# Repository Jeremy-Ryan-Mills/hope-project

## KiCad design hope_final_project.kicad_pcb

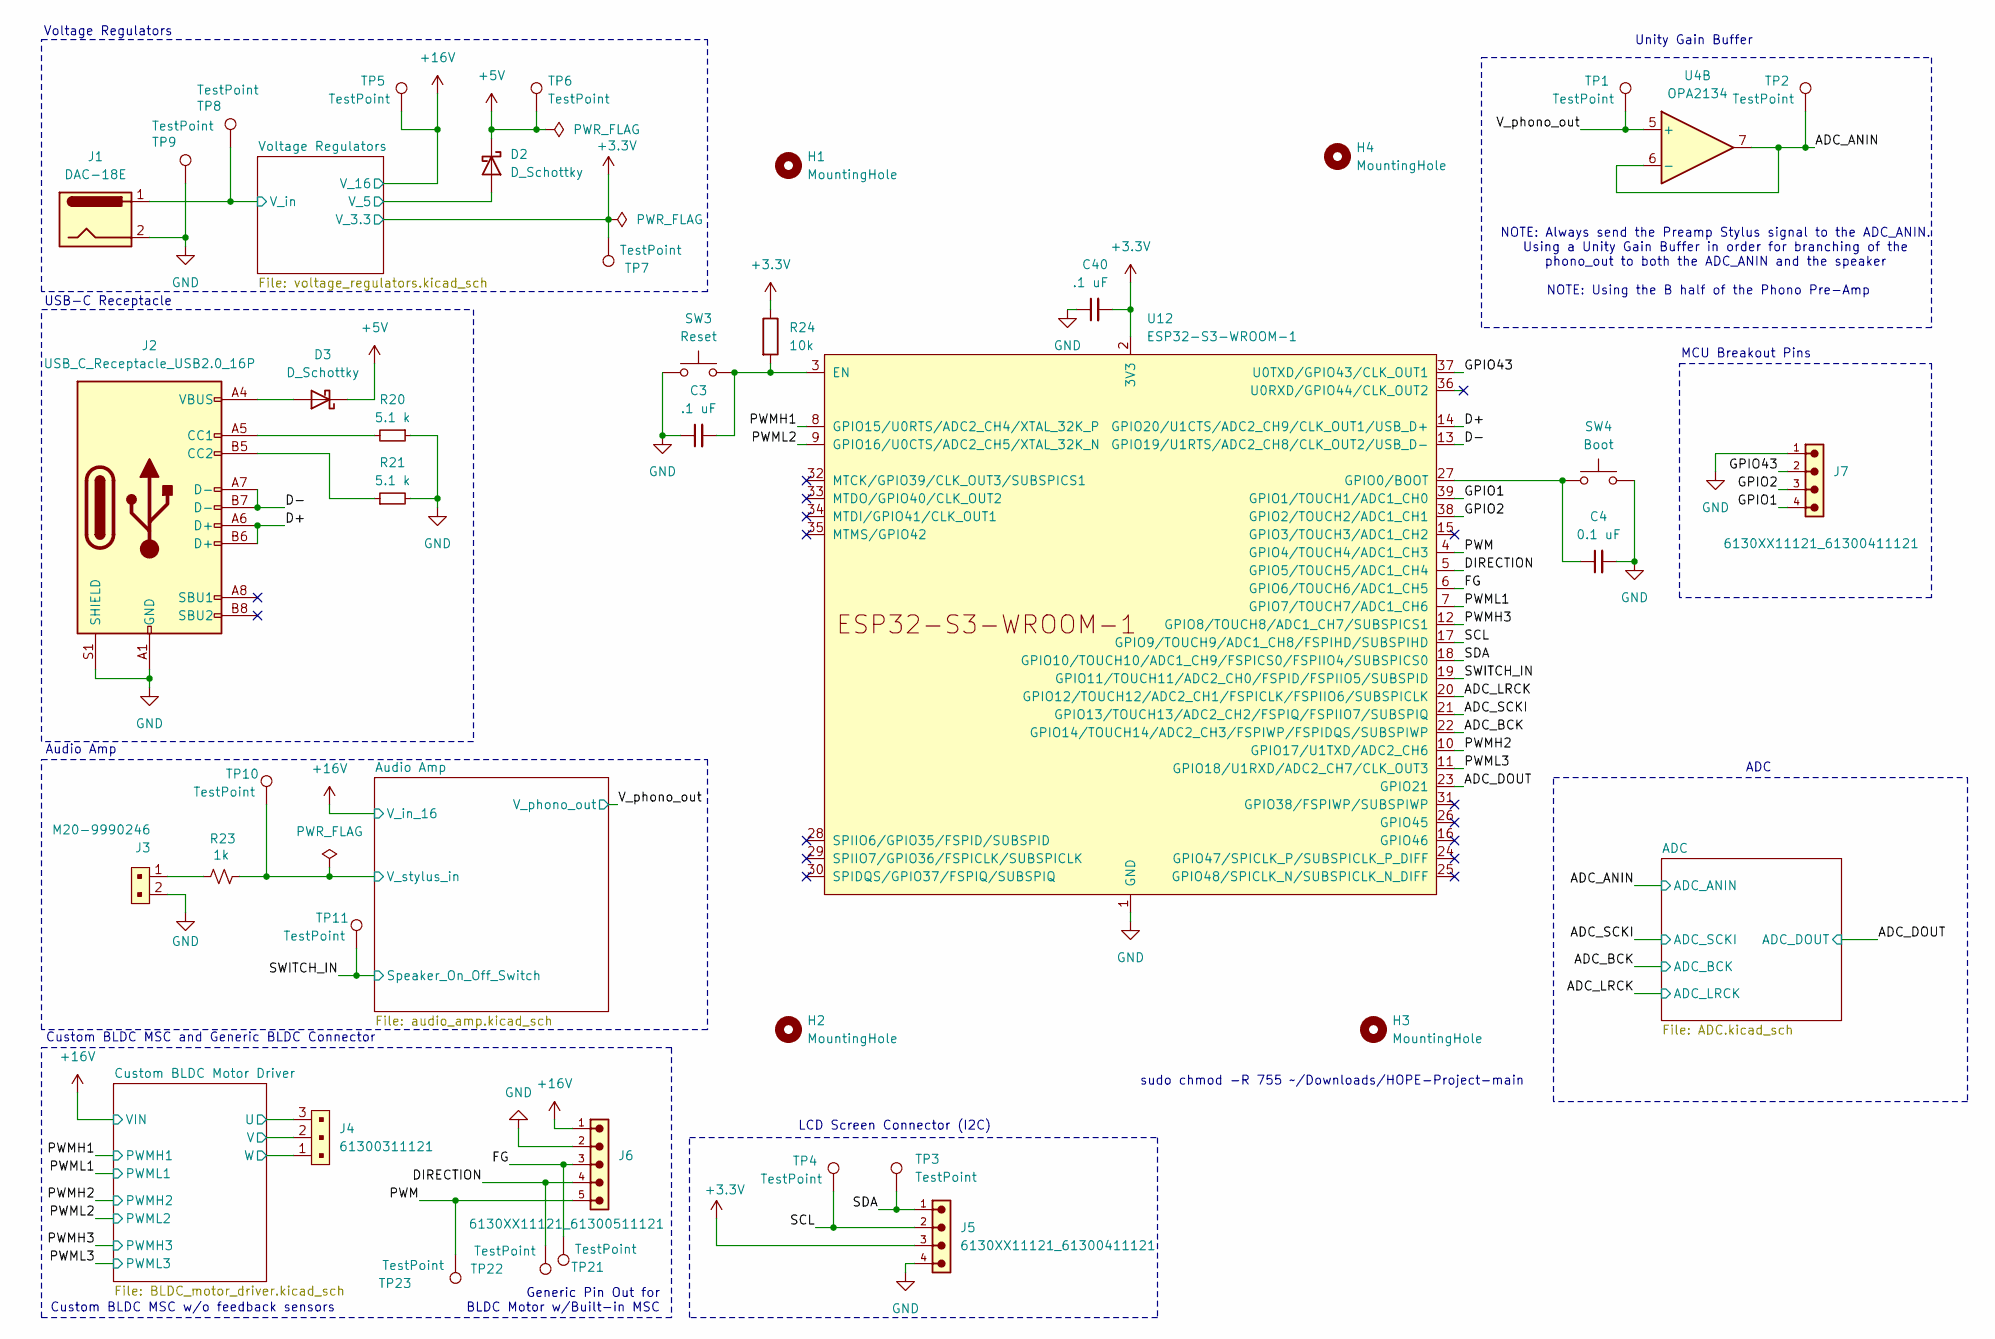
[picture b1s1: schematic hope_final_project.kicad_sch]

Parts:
C3, C40: .1 uF; C_0805_2012Metric
C4: 0.1 uF; C_0805_2012Metric
D2, D3: D_Schottky; D_SOD-123F
H1, H2, H3, H4: MountingHole; MountingHole_3.2mm_M3
J1: DAC-18E; PJ_002B
J2: USB_C_Receptacle_USB2.0_16P; GCT_USB4105GFA120
J3: M20-9990246; PinHeader_1x2_P2.54mm; MPN M20-9990246; Digi-Key_PN 952-2262-ND
J4: 61300311121; PinHeader_1x3_P2.54_Drill1.1mm; MPN 61300311121; Digi-Key_PN 732-5316-ND
J5, J7: 6130XX11121_61300411121; 61300411121; PART-NUMBER 61300411121
J6: 6130XX11121_61300511121; 61300511121; PART-NUMBER 61300511121
R20, R21: 5.1 k; R_0805_2012Metric
R23: 1k; R_0805_2012Metric
R24: 10k; R_0805_2012Metric
SW3: Reset; TL3301_A_G_EWI
SW4: Boot; TL3301_A_G_EWI
TP1, TP2, TP3, TP4, TP5, TP6, TP7, TP8, TP9, TP10, TP11, TP21, TP22, TP23: TestPoint; TestPoint_Pad_1.5x1.5mm
U4: OPA2134; SOIC-8_W3.9mm
U12: ESP32-S3-WROOM-1

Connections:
+3.3V: C40.2, J5.3, R24.1, TP7.1, U12.2 (3V3); also elsewhere on the board
+5V: D2.1 (K), D3.1 (K), TP6.1; also elsewhere on the board
+16V: J6.1, TP5.1; also elsewhere on the board
/ADC_ANIN: TP2.1, U4.6 (-), U4.7; also elsewhere on the board
/ADC_BCK: U12.22 (GPIO14/TOUCH14/ADC2_CH3/FSPIWP/FSPIDQS/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); also elsewhere on the board
/ADC_DOUT: U12.23 (GPIO21); also elsewhere on the board
/ADC_LRCK: U12.20 (GPIO12/TOUCH12/ADC2_CH1/FSPICLK/FSPIIO6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); also elsewhere on the board
/ADC_SCKI: U12.21 (GPIO13/TOUCH13/ADC2_CH2/FSPIQ/FSPIIO7/S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); also elsewhere on the board
/Audio Amp/V_stylus_in: R23.1, TP10.1; also elsewhere on the board
/Custom BLDC Motor Driver/VOUT_1: J4.3; also elsewhere on the board
/Custom BLDC Motor Driver/VOUT_2: J4.2; also elsewhere on the board
/Custom BLDC Motor Driver/VOUT_3: J4.1; also elsewhere on the board
/D+: J2.A6 (D+), J2.B6 (D+), U12.14 (GPIO20/U1CTS/ADC2_CH9/CLK_OUT1/USB_D+)
/D-: J2.A7 (D-), J2.B7 (D-), U12.13 (GPIO19/U1RTS/ADC2_CH8/CLK_OUT2/USB_D-)
/DIRECTION: J6.4, TP22.1, U12.5 (GPIO5/TOUCH5/ADC1_CH4)
/FG: J6.3, TP21.1, U12.6 (GPIO6/TOUCH6/ADC1_CH5)
/GPIO1: J7.4, U12.39 (GPIO1/TOUCH1/ADC1_CH0)
/GPIO2: J7.3, U12.38 (GPIO2/TOUCH2/ADC1_CH1)
/GPIO43: J7.2, U12.37 (U0TXD/GPIO43/CLK_OUT1)
/PWM: J6.5, TP23.1, U12.4 (GPIO4/TOUCH4/ADC1_CH3)
/PWMH1: U12.8 (GPIO15/U0RTS/ADC2_CH4/XTAL_32K_P); also elsewhere on the board
/PWMH2: U12.10 (GPIO17/U1TXD/ADC2_CH6); also elsewhere on the board
/PWMH3: U12.12 (GPIO8/TOUCH8/ADC1_CH7/SUBSPICS1); also elsewhere on the board
/PWML1: U12.7 (GPIO7/TOUCH7/ADC1_CH6); also elsewhere on the board
/PWML2: U12.9 (GPIO16/U0CTS/ADC2_CH5/XTAL_32K_N); also elsewhere on the board
/PWML3: U12.11 (GPIO18/U1RXD/ADC2_CH7/CLK_OUT3); also elsewhere on the board
/SCL: J5.2, TP4.1, U12.17 (GPIO9/TOUCH9/ADC1_CH8/FSPIHD/SUBSPIHD)
/SDA: J5.1, TP3.1, U12.18 (GPIO10/TOUCH10/ADC1_CH9/FSPICS0/FSPIIO4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)
/SWITCH_IN: TP11.1, U12.19 (GPIO11/TOUCH11/ADC2_CH0/FSPID/FSPIIO5/S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); also elsewhere on the board
/V_phono_out: TP1.1, U4.5 (+); also elsewhere on the board
/Voltage Regulators/V_5: D2.2 (A); also elsewhere on the board
/Voltage Regulators/V_in: J1.1, TP8.1; also elsewhere on the board
GND: C3.1, C4.2, C40.1, J1.2, J2.A1 (GND), J2.A12 (GND), J2.B1 (GND), J2.B12 (GND), J2.S1 (SHIELD), J3.2, J5.4, J6.2, J7.1, R20.1, R21.2, SW3.1 (A), SW3.2 (A), SW4.3 (B), SW4.4 (B), TP9.1, U12.1 (GND), U12.40 (GND), U12.41 (GND); also elsewhere on the board
unnamed: D3.2 (A), J2.A4 (VBUS), J2.A9 (VBUS), J2.B4 (VBUS), J2.B9 (VBUS)
unnamed: J2.A5 (CC1), R20.2
unnamed: J2.B5 (CC2), R21.1
unnamed: J3.1, R23.2
unnamed: C3.2, R24.2, SW3.3 (B), SW3.4 (B), U12.3 (EN)
unnamed: C4.1, SW4.1 (A), SW4.2 (A), U12.27 (GPIO0/BOOT)

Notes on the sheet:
Custom BLDC MSC w/o feedback sensors
Audio Amp
Unity Gain Buffer
MCU Breakout Pins
NOTE: Using the B half of the Phono Pre-Amp
USB-C Receptacle
LCD Screen Connector (I2C)
Custom BLDC MSC and Generic BLDC Connector
Generic Pin Out for BLDC Motor w/Built-in MSC
ADC
Voltage Regulators
NOTE: Always send the Preamp Stylus signal to the ADC_ANIN. Using a Unity Gain Buffer in order for branching of the phono_out to both the ADC_ANIN and the speaker
sudo chmod -R 755 ~/Downloads/HOPE-Project-main

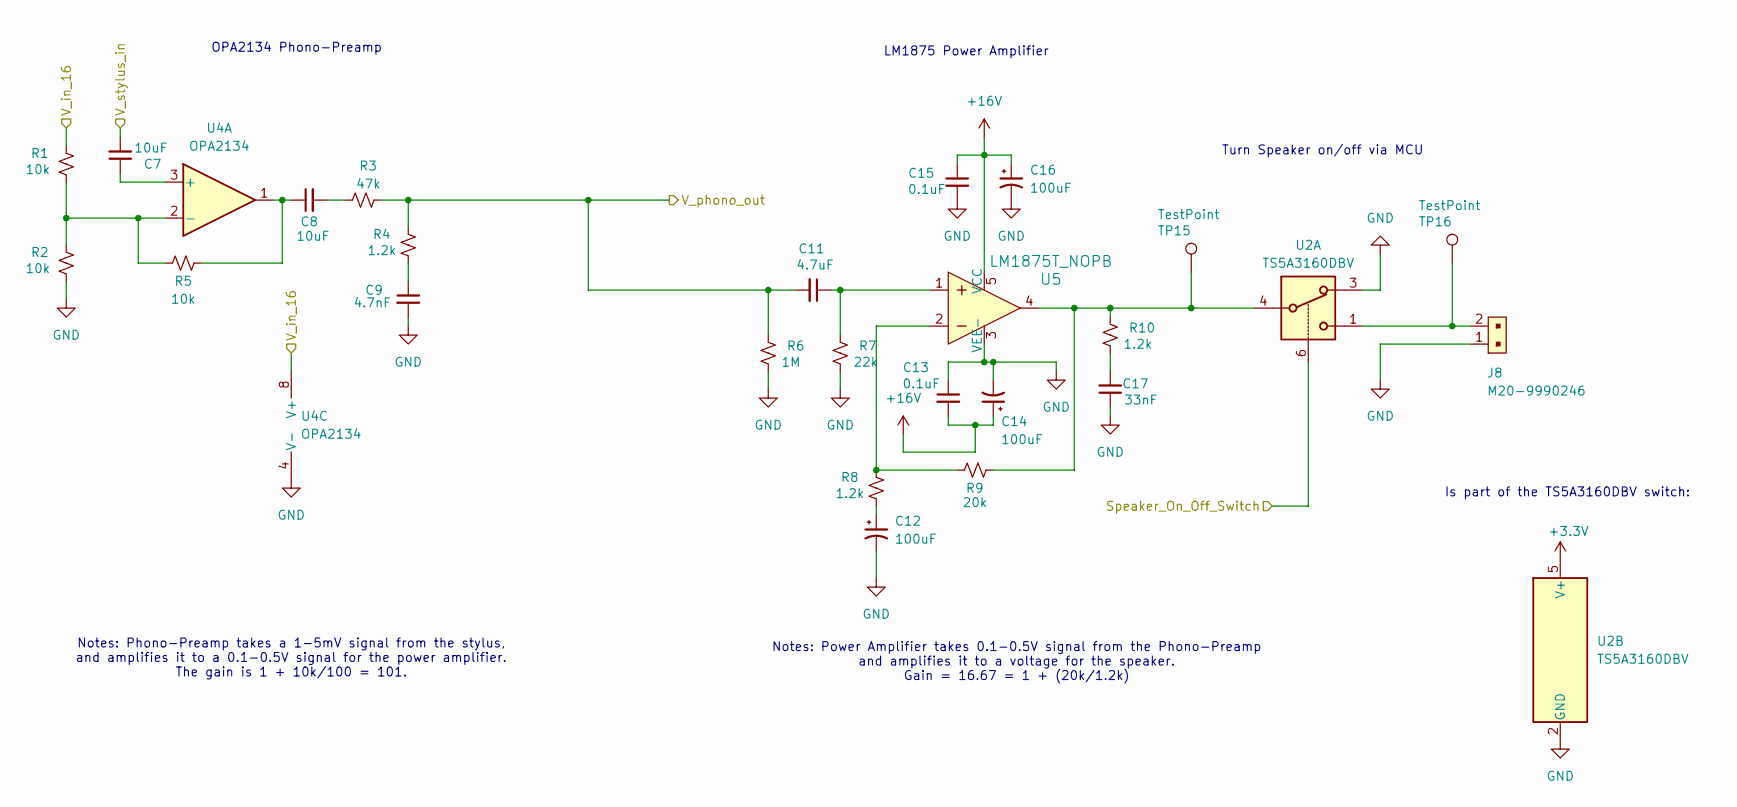
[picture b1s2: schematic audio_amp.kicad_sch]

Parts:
C7, C8: 10uF; C_0805_2012Metric
C9: 4.7nF; C_0805_2012Metric
C11: 4.7uF; C_0805_2012Metric
C12, C14, C16: 100uF; C_Radial_D8.0mm_H11.5mm_P3.50mm
C13, C15: 0.1uF; C_0805_2012Metric
C17: 33nF; C_0805_2012Metric
J8: M20-9990246; PinHeader_1x2_P2.54mm; MPN M20-9990246; Digi-Key_PN 952-2262-ND
R1, R2, R5: 10k; R_0805_2012Metric
R3: 47k; R_0805_2012Metric
R4, R8, R10: 1.2k; R_0805_2012Metric
R6: 1M; R_0805_2012Metric
R7: 22k; R_0805_2012Metric
R9: 20k; R_0805_2012Metric
TP15, TP16: TestPoint; TestPoint_Pad_1.5x1.5mm
U2: TS5A3160DBV; SOT-23-6
U4: OPA2134; SOIC-8_W3.9mm
U5: LM1875T_NOPB; TO-220-5; MPN LM1875T/NOPB; Digi-Key_PN LM1875T/NOPB-ND

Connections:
+3.3V: U2.5 (V+); also elsewhere on the board
+16V: C13.2, C14.1, C15.1, C16.1, R1.1, U4.8 (V+), U5.5 (VCC); also elsewhere on the board
/Audio Amp/V_stylus_in: C7.2; also elsewhere on the board
/SWITCH_IN: U2.6; also elsewhere on the board
/V_phono_out: C11.2, R3.2, R4.1, R6.1; also elsewhere on the board
GND: C9.2, C12.2, C13.1, C14.2, C15.2, C16.2, C17.1, J8.1, R2.2, R6.2, R7.2, U2.2 (GND), U2.3, U4.4 (V-), U5.3 (VEE-); also elsewhere on the board
unnamed: C8.1, R5.2, U4.1
unnamed: C8.2, R3.1
unnamed: C9.1, R4.2
unnamed: C11.1, R7.1, U5.1
unnamed: C12.1, R8.2
unnamed: C17.2, R10.2
unnamed: J8.2, TP16.1, U2.1
unnamed: R8.1, R9.1, U5.2
unnamed: R9.2, R10.1, TP15.1, U2.4, U5.4
unnamed: C7.1, U4.3 (+)
unnamed: R1.2, R2.1, R5.1, U4.2 (-)

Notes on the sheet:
OPA2134 Phono-Preamp
Is part of the TS5A3160DBV switch:
LM1875 Power Amplifier
Notes: Phono-Preamp takes a 1-5mV signal from the stylus, and amplifies it to a 0.1-0.5V signal for the power amplifier. The gain is 1 + 10k/100 = 101.
Notes: Power Amplifier takes 0.1-0.5V signal from the Phono-Preamp and amplifies it to a voltage for the speaker. Gain = 16.67 = 1 + (20k/1.2k)
Turn Speaker on/off via MCU

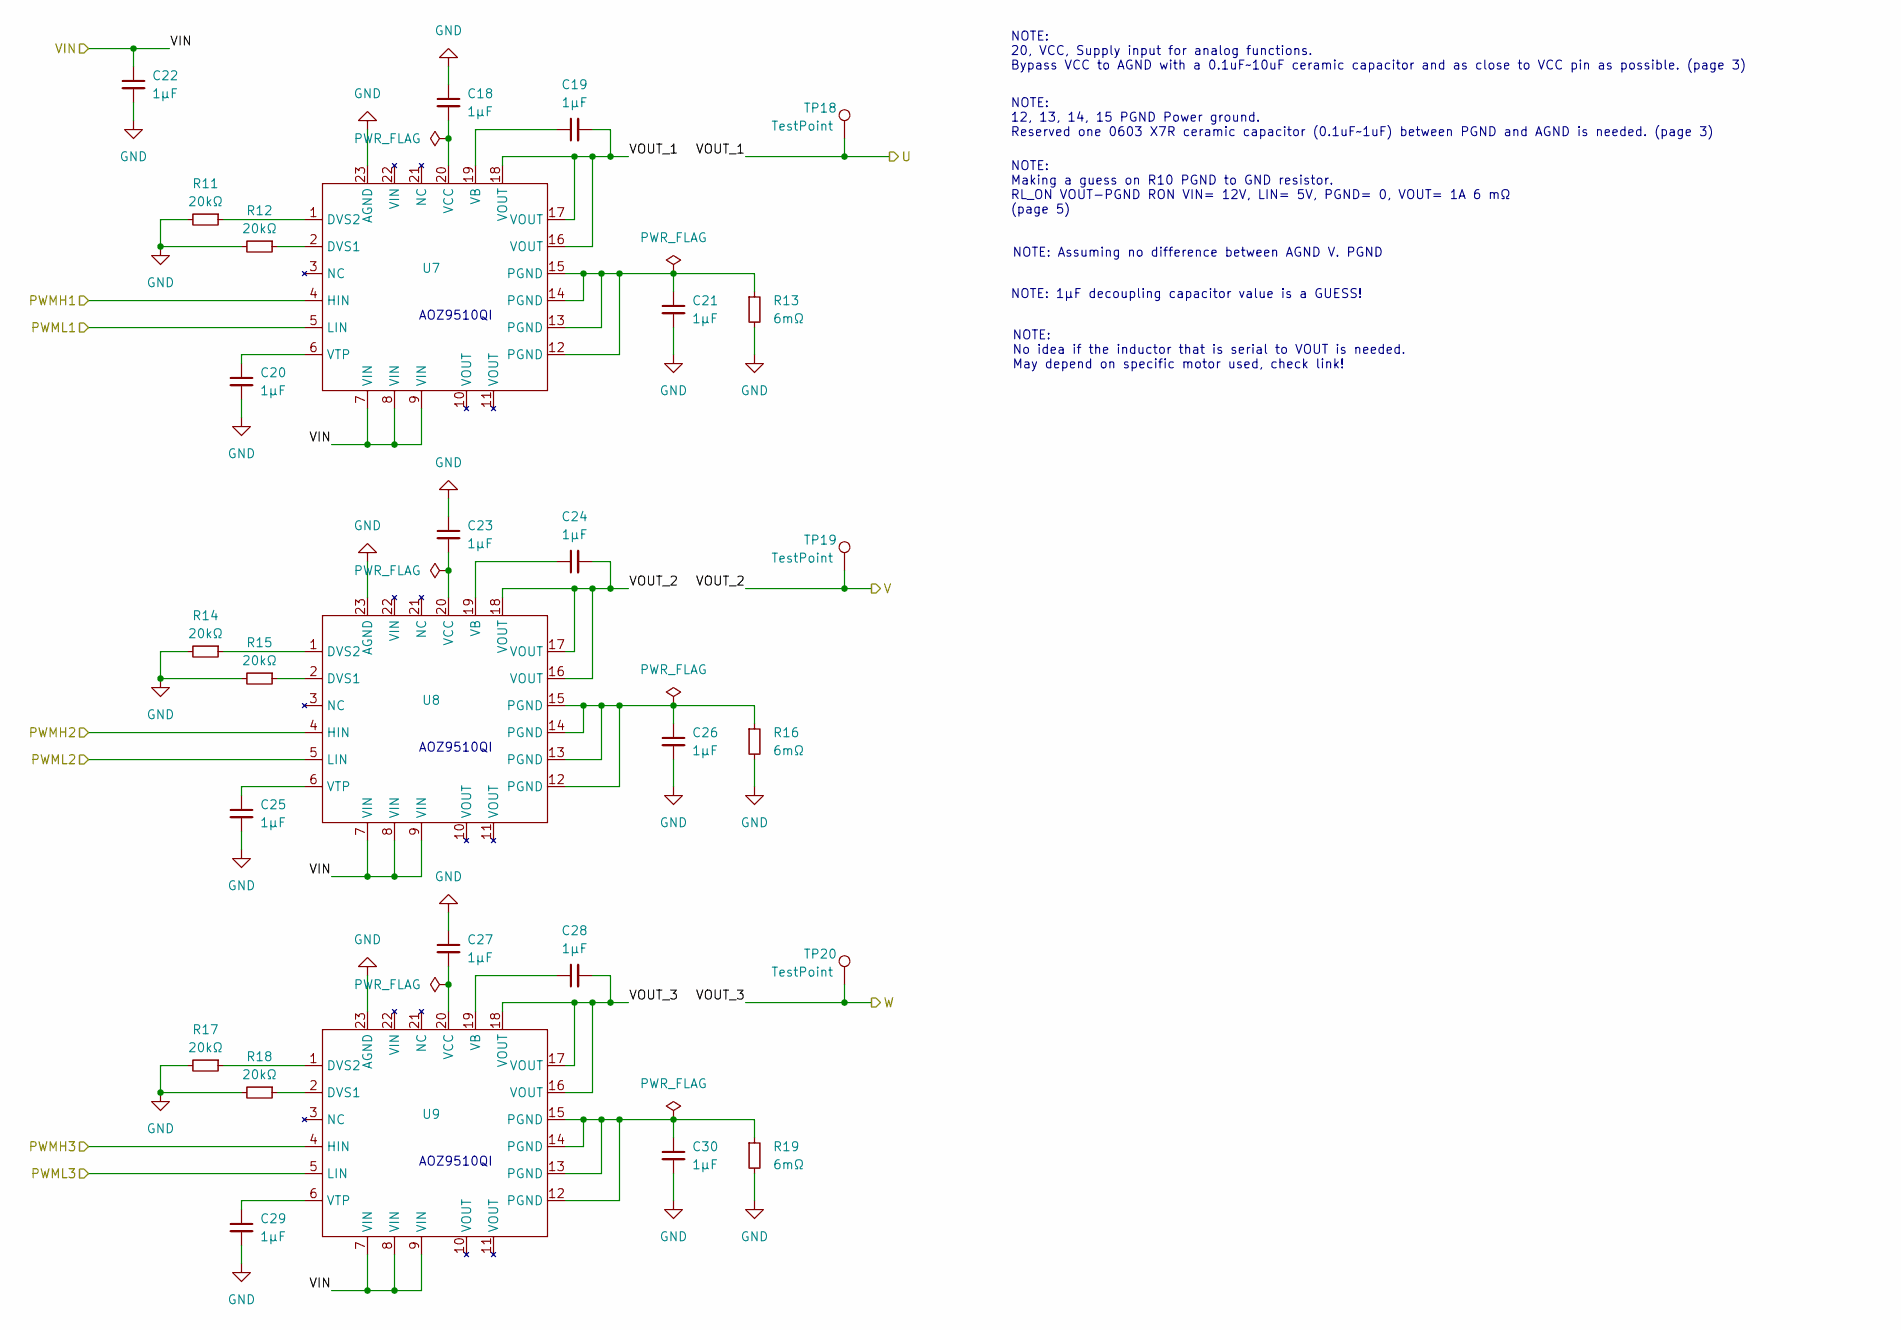
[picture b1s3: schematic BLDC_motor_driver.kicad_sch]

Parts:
C18, C19, C20, C21, C22, C23, C24, C25, C26, C27, C28, C29, C30: 1µF; C_0805_2012Metric
R11, R12, R14, R15, R17, R18: 20kΩ; R_0805_2012Metric
R13, R16, R19: 6mΩ; R_0805_2012Metric
TP18, TP19, TP20: TestPoint; TestPoint_Pad_1.5x1.5mm
U7, U8, U9: QFN-24-1EP_4x4mm_P0.5mm_EP2.7x2.7mm

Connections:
+16V: C22.1, U7.7 (VIN), U7.8 (VIN), U7.9 (VIN), U8.7 (VIN), U8.8 (VIN), U8.9 (VIN), U9.7 (VIN), U9.8 (VIN), U9.9 (VIN); also elsewhere on the board
/Custom BLDC Motor Driver/VOUT_1: C19.2, TP18.1, U7.16 (VOUT), U7.17 (VOUT), U7.18 (VOUT); also elsewhere on the board
/Custom BLDC Motor Driver/VOUT_2: C24.2, TP19.1, U8.16 (VOUT), U8.17 (VOUT), U8.18 (VOUT); also elsewhere on the board
/Custom BLDC Motor Driver/VOUT_3: C28.2, TP20.1, U9.16 (VOUT), U9.17 (VOUT), U9.18 (VOUT); also elsewhere on the board
/PWMH1: U7.4 (HIN); also elsewhere on the board
/PWMH2: U8.4 (HIN); also elsewhere on the board
/PWMH3: U9.4 (HIN); also elsewhere on the board
/PWML1: U7.5 (LIN); also elsewhere on the board
/PWML2: U8.5 (LIN); also elsewhere on the board
/PWML3: U9.5 (LIN); also elsewhere on the board
GND: C18.1, C20.2, C21.2, C22.2, C23.1, C25.2, C26.2, C27.1, C29.2, C30.2, R11.2, R12.2, R13.2, R14.2, R15.2, R16.2, R17.2, R18.2, R19.2, U7.23 (AGND), U8.23 (AGND), U9.23 (AGND); also elsewhere on the board
unnamed: C21.1, R13.1, U7.12 (PGND), U7.13 (PGND), U7.14 (PGND), U7.15 (PGND)
unnamed: C26.1, R16.1, U8.12 (PGND), U8.13 (PGND), U8.14 (PGND), U8.15 (PGND)
unnamed: C30.1, R19.1, U9.12 (PGND), U9.13 (PGND), U9.14 (PGND), U9.15 (PGND)
unnamed: R12.1, U7.2 (DVS1)
unnamed: R11.1, U7.1 (DVS2)
unnamed: C19.1, U7.19 (VB)
unnamed: C18.2, U7.20 (VCC)
unnamed: C20.1, U7.6 (VTP)
unnamed: R15.1, U8.2 (DVS1)
unnamed: R14.1, U8.1 (DVS2)
unnamed: C24.1, U8.19 (VB)
unnamed: C23.2, U8.20 (VCC)
unnamed: C25.1, U8.6 (VTP)
unnamed: R18.1, U9.2 (DVS1)
unnamed: R17.1, U9.1 (DVS2)
unnamed: C28.1, U9.19 (VB)
unnamed: C27.2, U9.20 (VCC)
unnamed: C29.1, U9.6 (VTP)

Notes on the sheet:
NOTE: 20, VCC, Supply input for analog functions. Bypass VCC to AGND with a 0.1uF~10uF ceramic capacitor and as close to VCC pin as possible. (page 3)
NOTE: 12, 13, 14, 15 PGND Power ground. Reserved one 0603 X7R ceramic capacitor (0.1uF~1uF) between PGND and AGND is needed. (page 3)
NOTE: No idea if the inductor that is serial to VOUT is needed. May depend on specific motor used, check link!
AOZ9510QI
NOTE: Making a guess on R10 PGND to GND resistor. RL_ON VOUT-PGND RON VIN= 12V, LIN= 5V, PGND= 0, VOUT= 1A 6 mΩ (page 5)
NOTE: Assuming no difference between AGND V. PGND
NOTE: 1µF decoupling capacitor value is a GUESS!

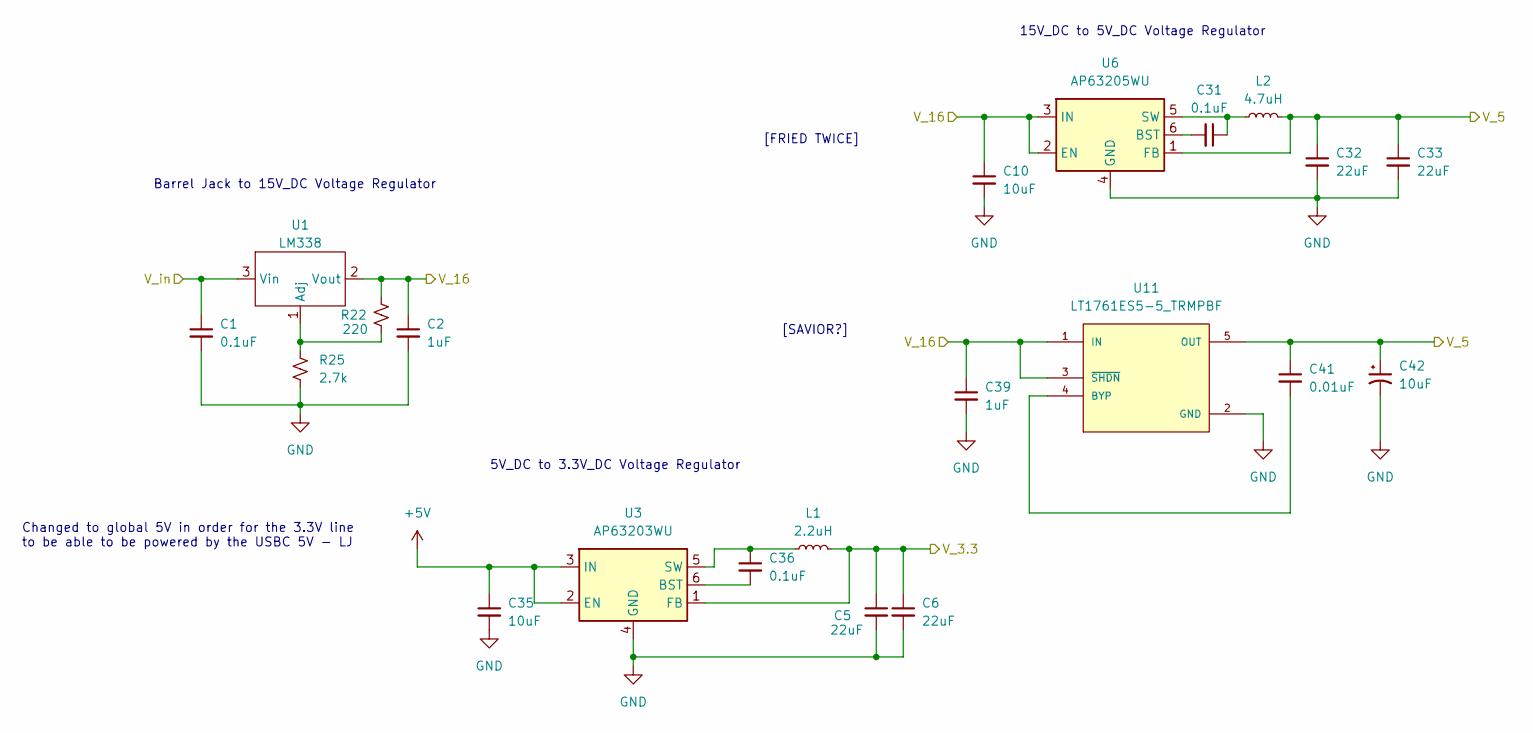
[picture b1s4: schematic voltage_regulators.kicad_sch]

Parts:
C1, C31, C36: 0.1uF; C_0805_2012Metric
C2, C39: 1uF; C_0805_2012Metric
C5, C6, C32, C33: 22uF; C_0805_2012Metric
C10, C35: 10uF; C_0805_2012Metric
C41: 0.01uF; C_0805_2012Metric
C42: 10uF; C_Radial_D8.0mm_H11.5mm_P3.50mm
L1: 2.2uH; L_1008_2520Metric
L2: 4.7uH; L_1210_3225Metric
R22: 220; R_0805_2012Metric
R25: 2.7k; R_0805_2012Metric
U1: LM338; TO-220-3
U3: AP63203WU; TSOT-23-6
U6: AP63205WU; TSOT-23-6
U11: LT1761ES5-5_TRMPBF; SOT95P280X100-5N; PARTREV F

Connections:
+3.3V: C5.1, C6.1, L1.2, U3.1 (FB); also elsewhere on the board
+5V: C35.1, U3.2 (EN), U3.3 (IN); also elsewhere on the board
+16V: C2.1, C10.1, C39.1, R22.1, U1.2 (Vout), U6.2 (EN), U6.3 (IN), U11.1 (IN), U11.3 (~SHDN); also elsewhere on the board
/Voltage Regulators/V_5: C32.1, C33.1, C41.1, C42.1, L2.2, U6.1 (FB), U11.5 (OUT); also elsewhere on the board
/Voltage Regulators/V_in: C1.1, U1.3 (Vin); also elsewhere on the board
GND: C1.2, C2.2, C5.2, C6.2, C10.2, C32.2, C33.2, C35.2, C39.2, C42.2, R25.2, U3.4 (GND), U6.4 (GND), U11.2 (GND); also elsewhere on the board
unnamed: R22.2, R25.1, U1.1 (Adj)
unnamed: C36.2, U3.6 (BST)
unnamed: C36.1, L1.1, U3.5 (SW)
unnamed: C31.2, U6.6 (BST)
unnamed: C31.1, L2.1, U6.5 (SW)
unnamed: C41.2, U11.4 (BYP)

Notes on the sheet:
Barrel Jack to 15V_DC Voltage Regulator
5V_DC to 3.3V_DC Voltage Regulator
[SAVIOR?]
Changed to global 5V in order for the 3.3V line to be able to be powered by the USBC 5V - LJ
15V_DC to 5V_DC Voltage Regulator
[FRIED TWICE]

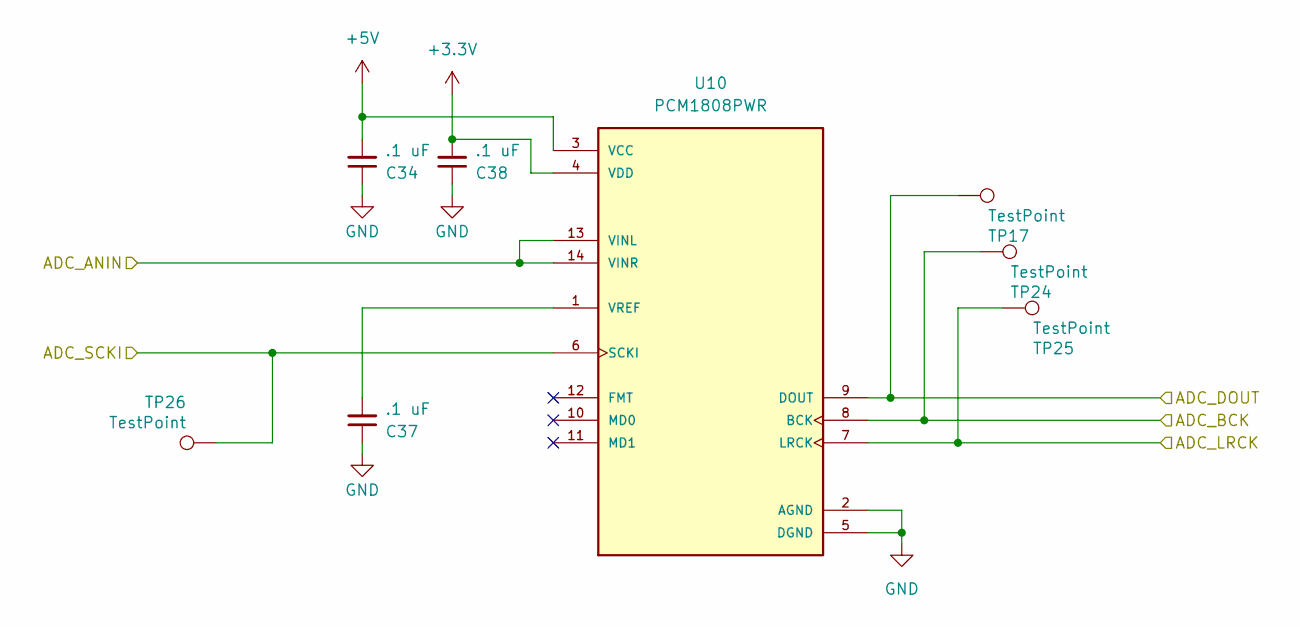
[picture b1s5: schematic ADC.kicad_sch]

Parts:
C34, C37, C38: .1 uF; C_0805_2012Metric
TP17, TP24, TP25, TP26: TestPoint; TestPoint_Pad_1.5x1.5mm
U10: PCM1808PWR; SOP65P640X120-14N; PARTREV B

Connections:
+3.3V: C38.2, U10.4 (VDD); also elsewhere on the board
+5V: C34.2, U10.3 (VCC); also elsewhere on the board
/ADC_ANIN: U10.13 (VINL), U10.14 (VINR); also elsewhere on the board
/ADC_BCK: TP24.1, U10.8 (BCK); also elsewhere on the board
/ADC_DOUT: TP17.1, U10.9 (DOUT); also elsewhere on the board
/ADC_LRCK: TP25.1, U10.7 (LRCK); also elsewhere on the board
/ADC_SCKI: TP26.1, U10.6 (SCKI); also elsewhere on the board
GND: C34.1, C37.1, C38.1, U10.2 (AGND), U10.5 (DGND); also elsewhere on the board
unnamed: C37.2, U10.1 (VREF)

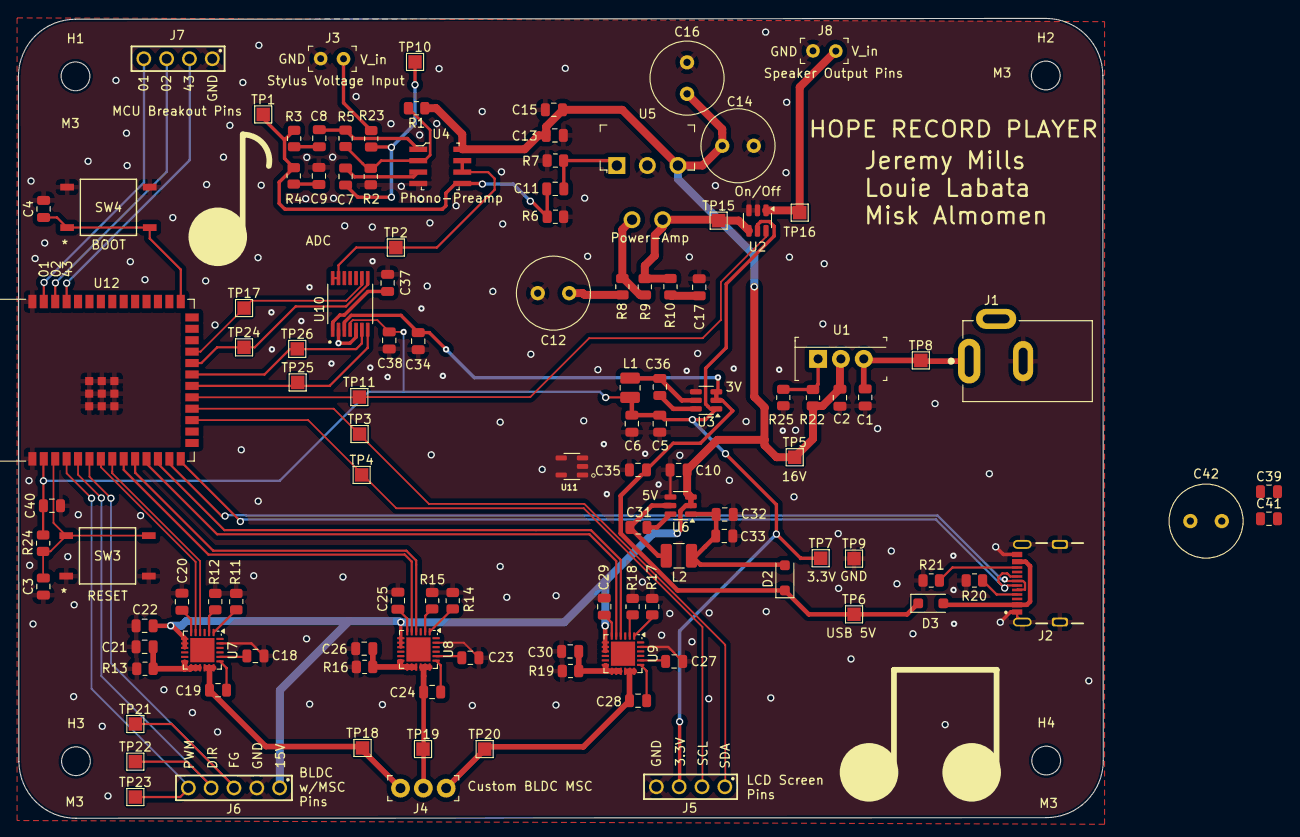
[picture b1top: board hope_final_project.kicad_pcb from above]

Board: 2 copper layers, 120.7 x 89.0 mm, 120 parts (0 on the bottom side), 75 nets.

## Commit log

2024-09-30 Created project
2024-10-01 Updated schematic for 230VAC to 15VAC regulator
2024-10-01 Completed 5V regulator and filled out values for both 15 and 5V regulators
2024-10-01 Commiting what I didn't save for last push
2024-10-01 Worked on Phono Preamp circuit
2024-10-02 Finished phono preamp and power amp, still subject to passive value changes
2024-10-03 block diagram
2024-10-10 Started working on motor drivers and MCU
2024-10-11 Seperated audio amp into a seperate sheet
2024-10-11 worked on audio amp and moved voltage regulators to a new sheet
2024-10-16 Finished audio amplifier, added 3.3V regulator,etc
2024-10-16 <MCU>
2024-10-17 added usb c receptacle
2024-10-18 Connected external DAC to MCU
2024-10-18 ADC and DAC
2024-10-19 Replaced 3.3V regulator
2024-10-19 Finishing touches for schematic turn in
2024-10-19 Added BOM
2024-10-26 Added footprints that already exist in the library
2024-10-26 Cleaning up footprint and starting layout
2024-10-27 worked on the layout
2024-10-27 Made some progress on the layout
2024-10-28 Working on layout and updated according to feedback from schematic
2024-10-28 Worked on Layout, connected motor drivers
2024-10-28 no more DRC errors
2024-10-28 updated Motor Controller layout and schematic a bit
2024-10-29 Work on headers and layout
2024-10-30 Fixed power
2024-10-30 Finished USB receptacle
2024-10-30 Attempting to switch over to ESP32-S3
2024-10-31 Beginning to add reset/boot buttons and power
2024-10-31 whatever else changes, forgot
2024-10-31 Added switching IC
2024-10-31 thickened traces
2024-11-01 Wrapped up layout, increased trace width
2024-11-01 Made uniform vias
2024-11-02 Made it so the 3.3V line can be powered by the 5V of the USBC
2024-11-02 added some power to S3 now in main
2024-11-02 added s3 footprint and finished adding s3 to schematic
2024-11-02 Cleaned up S3 schematic DRC errors
2024-11-02 Finished changes. submitting layout review
2024-11-02 final touches I forgot
2024-11-05 Updated schematic to include a LCD screen connector and added another connector for a BLDC motor w/built-in encoder
2024-11-05 added new components to layout from schematic update
2024-11-05 More layout changes
2024-11-05 Implemented schematic changes to layout (added screen and new MCU), implemented some feedback
2024-11-06 Added changes including unity gain buffer
2024-11-07 House Keeping
2024-11-07 Fixed power amplifier and voltage regulator situation
2024-11-07 safety commit
2024-11-07 decoupling capacitors
2024-11-08 Adjusting layout
2024-11-08 16V adjustments
2024-11-08 safety push
2024-11-08 Changed the footprint and schematic of the J5 J7 connectors to match BOM
2024-11-08 Changed another connector to fit BOM
2024-11-08 Final submission
2024-11-08 Fixing last minute DRC errors
2024-11-08 FINAL FINAL submission
2024-12-04 Starting some firmware coding
2024-12-07 Maybe could replace 5V buck with something else?
